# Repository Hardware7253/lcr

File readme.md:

# LCR Meter

## Description
This LCR meter is capable of measuring complex impedance of various passive components and features auto-ranging.
Figure 1 shows the basic test circuit and provides an equation that can be used to calculate the impedance of the DUT.
This circuit + additional filtering and biasing is used within the LCR design.
The MCU software uses the pk-pk values of the sampled waveforms for magnitudes, and calculates the phase difference using in-phase and quadrature components of the multiplied current and test voltage waveforms (v3 & v2). The IQ components are low-pass-filtered, then their arctan is taken to find the phase difference.

Figure 1: Basic LCR testing circuit.

## Demos

## Additional photos

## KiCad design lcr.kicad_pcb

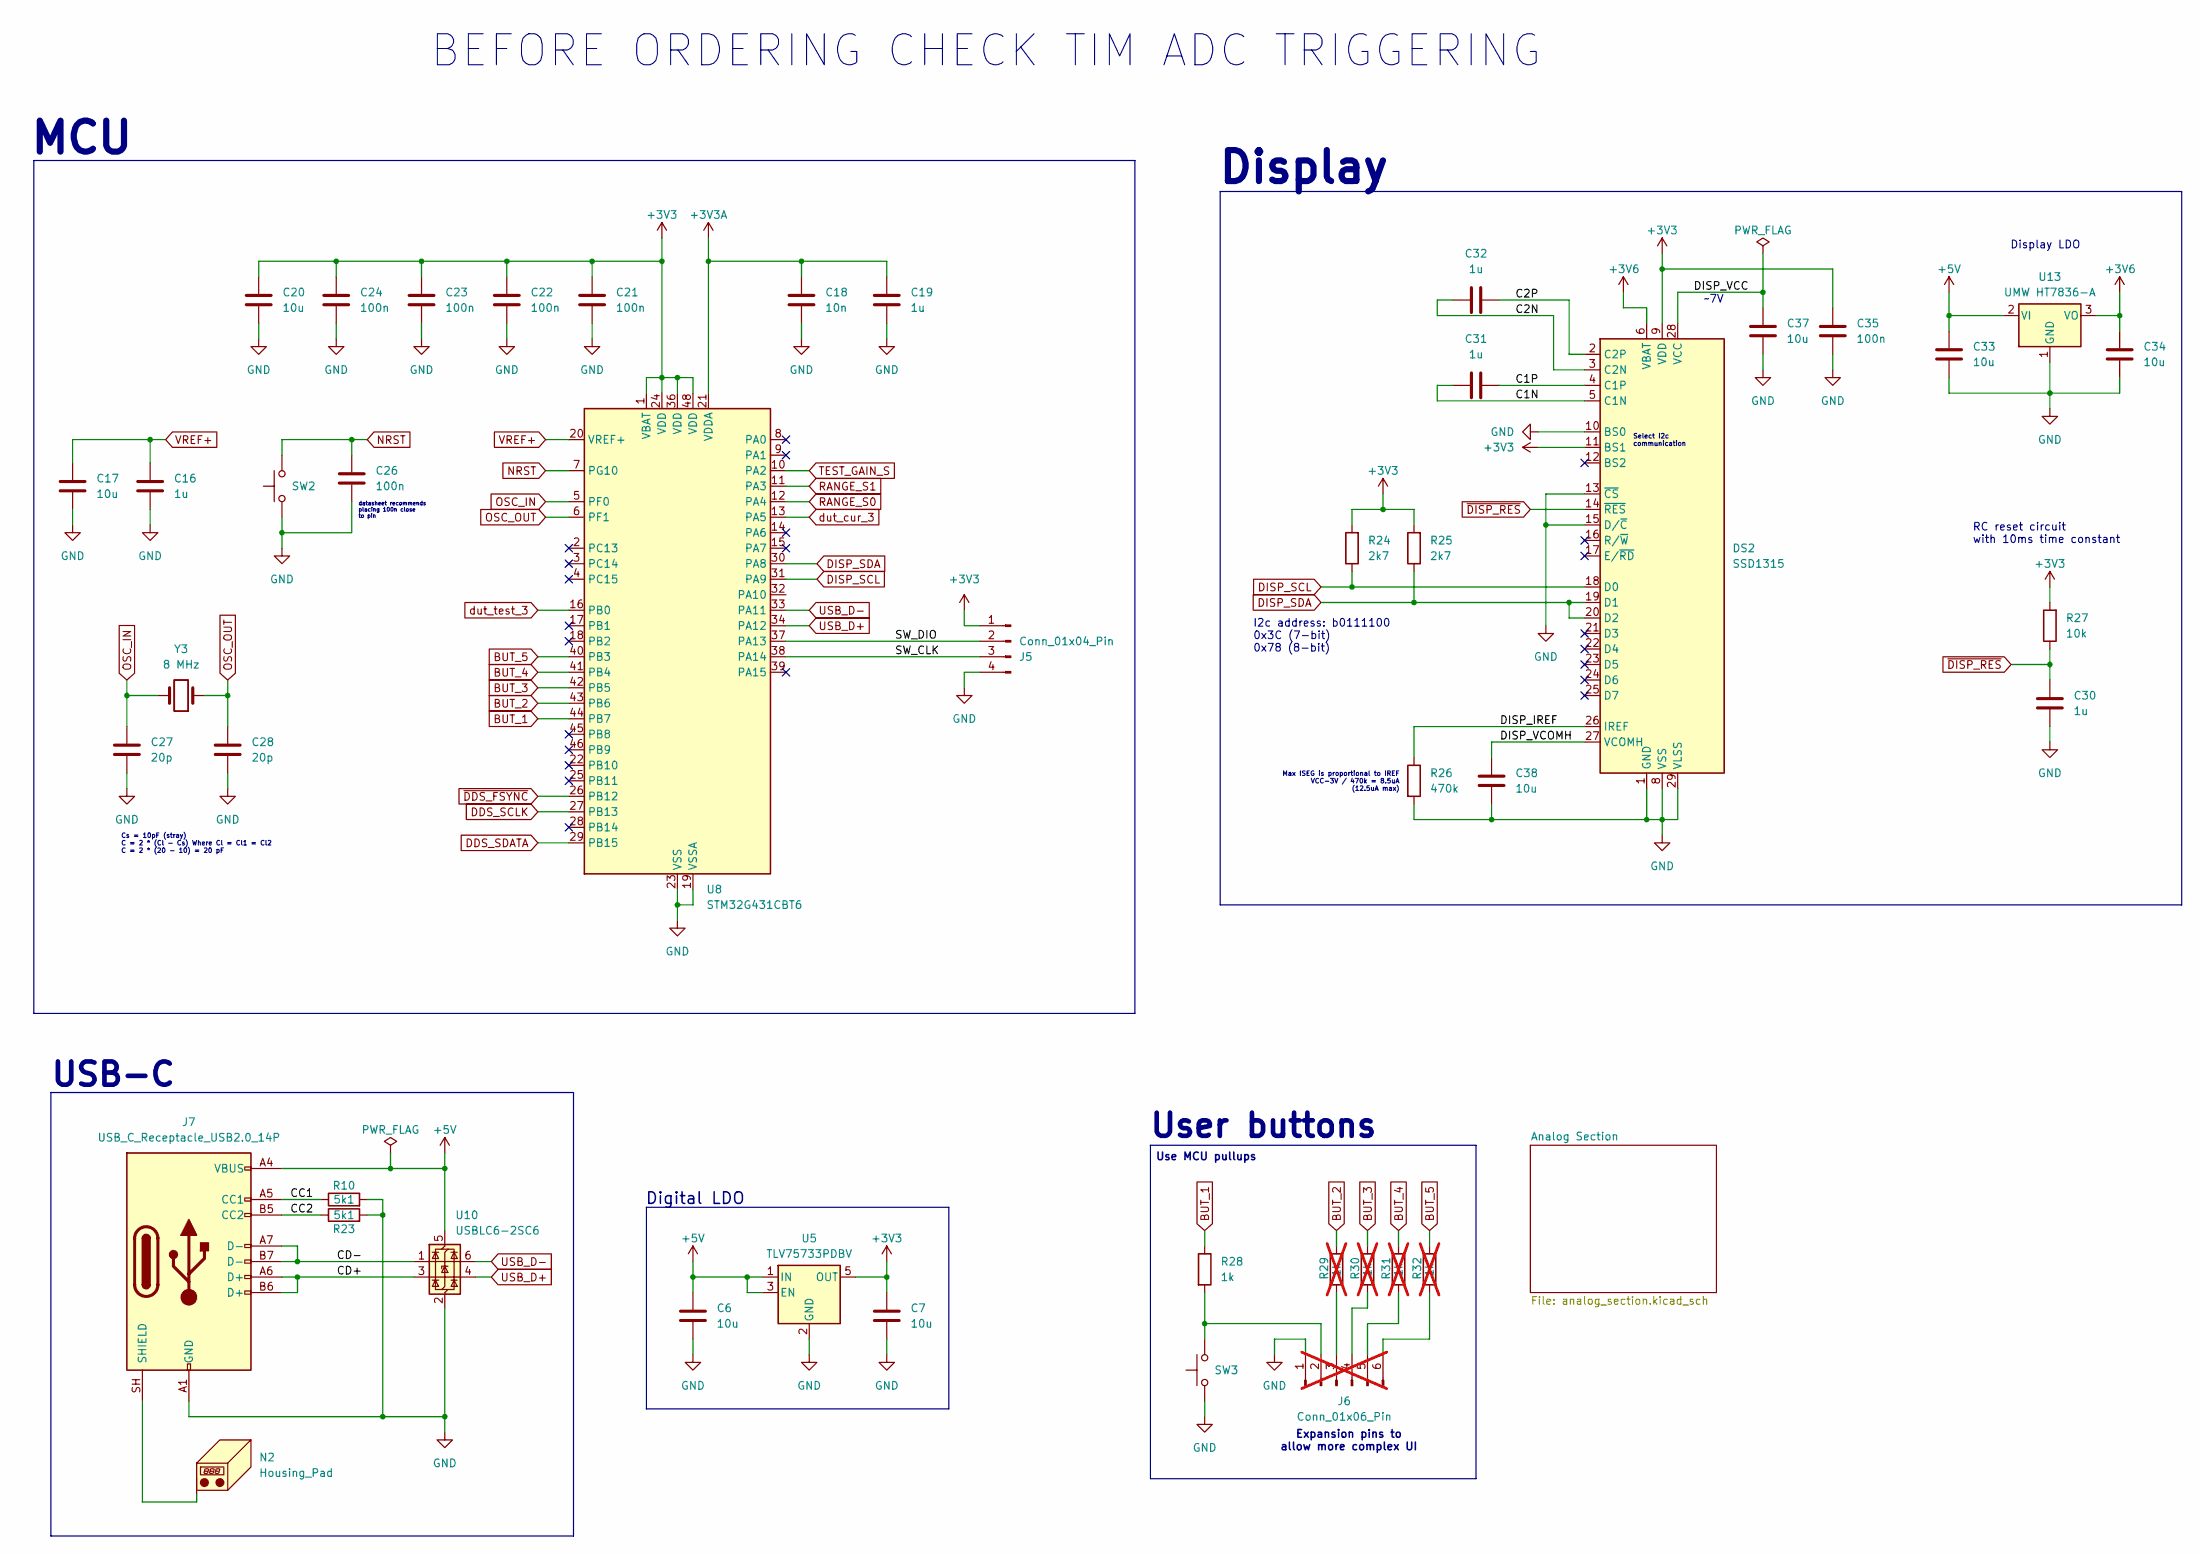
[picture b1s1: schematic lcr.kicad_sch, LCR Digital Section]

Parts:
C6, C7, C17, C20, C33, C34, C37, C38: 10u; C_0603_1608Metric; LCSC PART # C96446
C16, C19, C30, C31, C32: 1u; C_0603_1608Metric; LCSC PART # C15849
C18: 10n; C_0603_1608Metric; LCSC PART # C57112
C21, C22, C23, C24, C26, C35: 100n; C_0603_1608Metric; LCSC PART # C14663
C27, C28: 20p; C_0603_1608Metric; LCSC PART # C326779
DS2: SSD1315; 0.96 Inch OLED Display; LCSC PART # C18723027/C262645
J5: Conn_01x04_Pin; PinHeader_1x04_P2.54mm_Vertical
J6: Conn_01x06_Pin; PinHeader_1x06_P2.54mm_Vertical; not fitted
J7: USB_C_Receptacle_USB2.0_14P; USB_TYPE-C-31-M-12; LCSC PART # C165948
N2: Housing_Pad; TestPoint_Pad_2.0x2.0mm
R10, R23: 5k1; R_0603_1608Metric; LCSC PART # C23186
R24, R25: 2k7; R_0603_1608Metric; LCSC PART # C114612
R26: 470k; R_0603_1608Metric; LCSC PART # C114622
R27: 10k; R_0603_1608Metric; LCSC PART # C25804
R28: 1k; R_0603_1608Metric; LCSC PART # C22548
R29, R30, R31, R32: 1k; R_0603_1608Metric; LCSC PART # C22548; not fitted
SW2, SW3: SW_Push; Korean Hroparts Elec K2-1107ST-A4DW-06; LCSC PART # C118141
U5: TLV75733PDBV; SOT-23-5; LCSC PART # C485517
U8: STM32G431CBT6; LQFP-48_7x7mm_P0.5mm; LCSC PART # C529355
U10: USBLC6-2SC6; SOT-23-6; LCSC PART # C7519
U13: UMW HT7836-A; SOT-89-3
Y3: 8 MHz; Crystal_SMD_5032-2Pin_5.0x3.2mm; LCSC PART # C46613796

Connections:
+3V3: C7.2, C20.2, C21.1, C22.1, C23.1, C24.1, C35.1, DS2.9 (VDD), DS2.11 (BS1), J5.1, R24.2, R25.2, R27.2, U5.5 (OUT), U8.1 (VBAT), U8.24 (VDD), U8.36 (VDD), U8.48 (VDD); also elsewhere on the board
+3V3A: C18.1, C19.1, U8.21 (VDDA); also elsewhere on the board
+3V6: C34.2, DS2.6 (VBAT), U13.3 (VO)
+5V: C6.2, C33.2, J7.A4 (VBUS), J7.A9 (VBUS), J7.B4 (VBUS), J7.B9 (VBUS), U5.1 (IN), U5.3 (EN), U10.5 (VBUS), U13.2 (VI); also elsewhere on the board
/C1N: C31.1, DS2.5 (C1N)
/C1P: C31.2, DS2.4 (C1P)
/C2N: C32.1, DS2.3 (C2N)
/C2P: C32.2, DS2.2 (C2P)
/CC1: J7.A5 (CC1), R10.1
/CC2: J7.B5 (CC2), R23.1
/CD+: J7.A6 (D+), J7.B6 (D+), U10.3 (I/O2)
/CD-: J7.A7 (D-), J7.B7 (D-), U10.1 (I/O1)
/DISP_IREF: DS2.26 (IREF), R26.1
/DISP_VCC: C37.2, DS2.28 (VCC)
/DISP_VCOMH: C38.2, DS2.27 (VCOMH)
/SW_CLK: J5.3, U8.38 (PA14)
/SW_DIO: J5.2, U8.37 (PA13)
BUT_1: R28.1, U8.44 (PB7)
BUT_2: R29.1, U8.43 (PB6)
BUT_3: R30.1, U8.42 (PB5)
BUT_4: R31.1, U8.41 (PB4)
BUT_5: R32.1, U8.40 (PB3)
DDS_SCLK: U8.27 (PB13); also elsewhere on the board
DDS_SDATA: U8.29 (PB15); also elsewhere on the board
DISP_SCL: DS2.18 (D0), R24.1, U8.31 (PA9)
DISP_SDA: DS2.19 (D1), DS2.20 (D2), R25.1, U8.30 (PA8)
GND: C6.1, C7.1, C16.2, C17.2, C18.2, C19.2, C20.1, C21.2, C22.2, C23.2, C24.2, C26.2, C27.2, C28.2, C30.2, C33.1, C34.1, C35.2, C37.1, C38.1, DS2.1 (GND), DS2.8 (VSS), DS2.10 (BS0), DS2.13 (~CS), DS2.15 (D/~C), DS2.29 (VLSS), DS2.30 (GND), J5.4, J6.1, J7.A1 (GND), J7.A12 (GND), J7.B1 (GND), J7.B12 (GND), R10.2, R23.2, R26.2, SW2.1, SW3.1, U5.2 (GND), U8.19 (VSSA), U8.23 (VSS), U8.35 (VSS), U8.47 (VSS), U10.2 (GND), U13.1 (GND); also elsewhere on the board
NRST: C26.1, SW2.2, U8.7 (PG10)
unnamed: J6.2, R28.2, SW3.2
unnamed: J6.3, R29.2
unnamed: J6.4, R30.2
unnamed: J6.5, R31.2
unnamed: J6.6, R32.2
unnamed: J7.SH (SHIELD), N2.1 (PAD_1)
OSC_IN: C27.1, U8.5 (PF0), Y3.2
OSC_OUT: C28.1, U8.6 (PF1), Y3.1
RANGE_S0: U8.12 (PA4); also elsewhere on the board
RANGE_S1: U8.11 (PA3); also elsewhere on the board
TEST_GAIN_S: U8.10 (PA2); also elsewhere on the board
USB_D+: U8.34 (PA12), U10.4 (I/O2)
USB_D-: U8.33 (PA11), U10.6 (I/O1)
VREF+: C16.1, C17.1, U8.20 (VREF+)
dut_cur_3: U8.13 (PA5); also elsewhere on the board
dut_test_3: U8.16 (PB0); also elsewhere on the board
~DDS_FSYNC: U8.26 (PB12); also elsewhere on the board
~DISP_RES: C30.1, DS2.14 (~RES), R27.1

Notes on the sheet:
Max ISEG is proportional to IREF VCC-3V / 470k = 8.5uA (12.5uA max)
Display LDO
Cs = 10pF (stray) C = 2 * (Cl - Cs) Where Cl = Cl1 = Cl2 C = 2 * (20 - 10) = 20 pF
User buttons
Digital LDO
I2c address: b0111100 0x3C (7-bit) 0x78 (8-bit)
USB-C
RC reset circuit with 10ms time constant
~7V
Use MCU pullups
Select i2c communication
MCU
datasheet recommends placing 100n close to pin
Expansion pins to allow more complex UI
Display
BEFORE ORDERING CHECK TIM ADC TRIGGERING

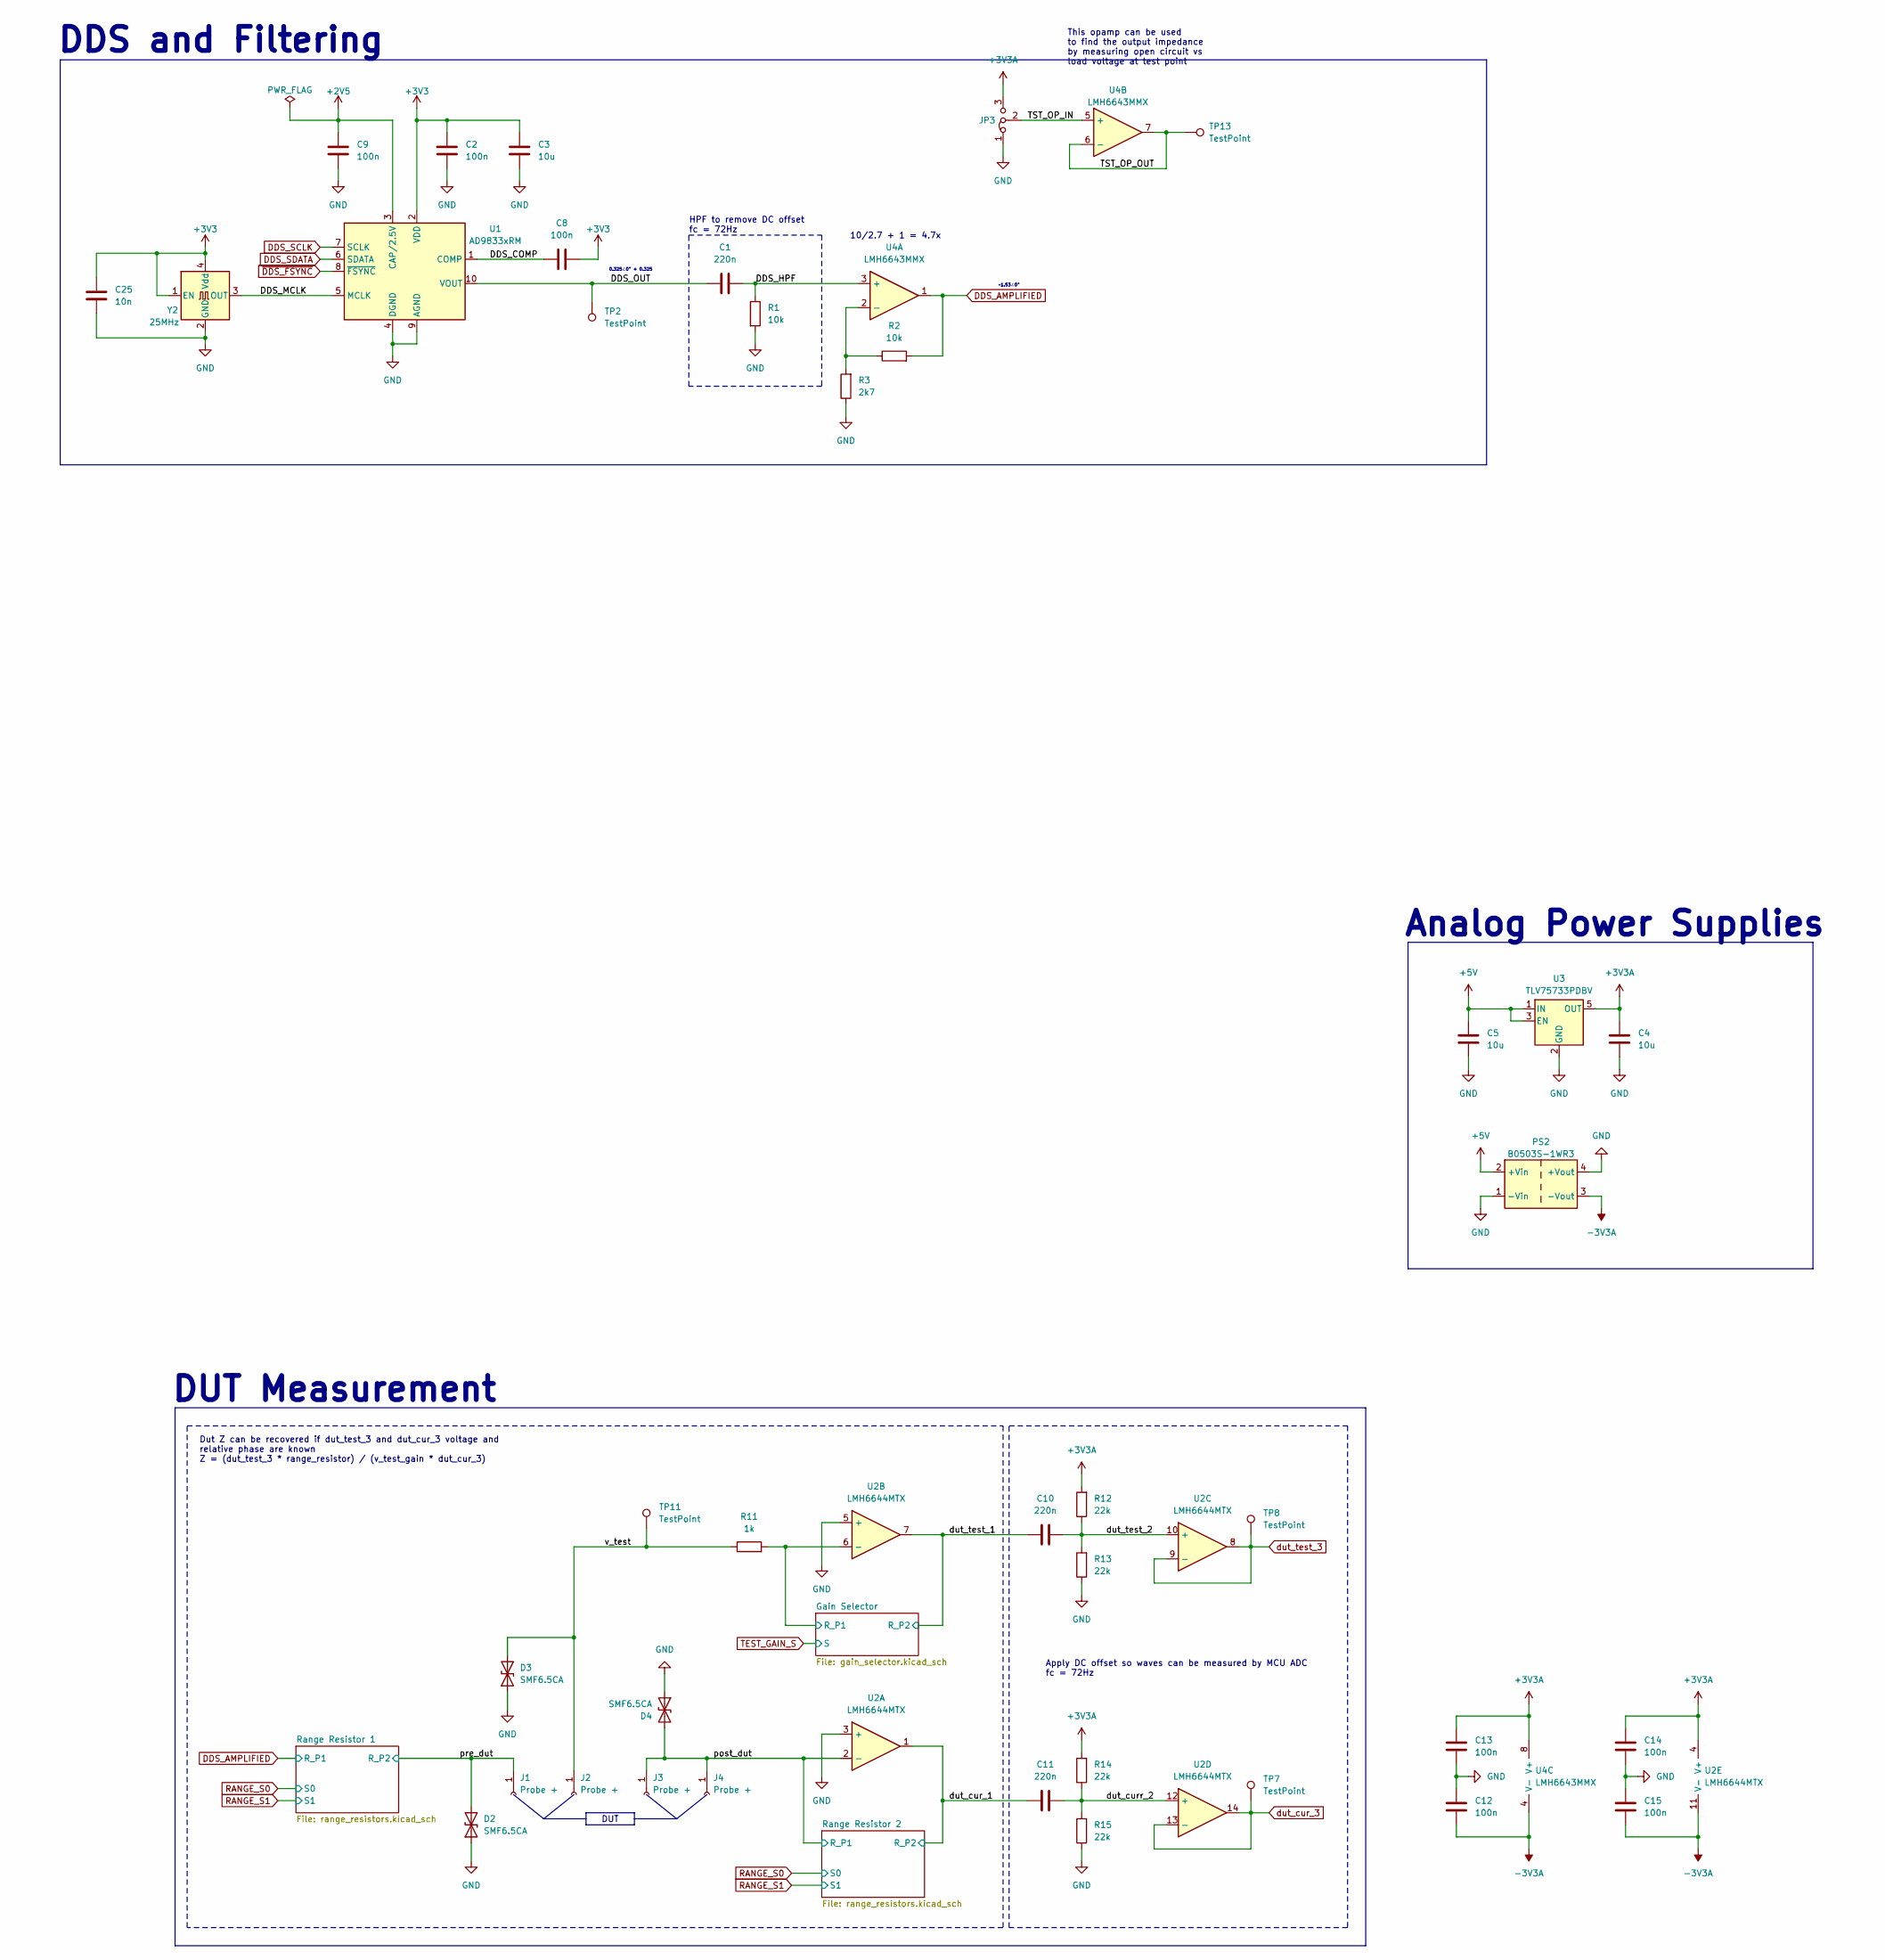
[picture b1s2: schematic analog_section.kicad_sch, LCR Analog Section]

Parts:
C1, C10, C11: 220n; C_0603_1608Metric; LCSC PART # C14663
C2, C8, C9, C12, C13, C14, C15: 100n; C_0603_1608Metric; LCSC PART # C14663
C3, C4, C5: 10u; C_0603_1608Metric; LCSC PART # C96446
C25: 10n; C_0603_1608Metric; LCSC PART # C57112
D2, D3, D4: SMF6.5CA; Nexperia_CFP3_SOD-123W; LCSC PART # C7466385
J1, J2: Probe +; Banana_Cliff_FCR7350R_S16N-PC_Horizontal; LCSC PART # C7437326
J3, J4: Probe +; Banana_Cliff_FCR7350B_S16N-PC_Horizontal; LCSC PART # C7437327
JP3: Jumper_3_Bridged12; PinHeader_1x03_P2.54mm_Vertical
PS2: B0503S-1WR3; Converter_DCDC_Murata_MEE1SxxxxSC_THT; LCSC PART # C7465187
R1, R2: 10k; R_0603_1608Metric; LCSC PART # C25804
R3: 2k7; R_0603_1608Metric; LCSC PART # C114612
R11: 1k; R_0603_1608Metric; LCSC PART # C22548
R12, R13, R14, R15: 22k; R_0603_1608Metric; LCSC PART # C114065
TP2, TP7, TP8, TP11, TP13: TestPoint; TestPoint_Keystone_5000-5004_Miniature; LCSC PART # C5199801
U1: AD9833xRM; MSOP-10_3x3mm_P0.5mm; LCSC PART # C9652
U2: LMH6644MTX; TSSOP-14_4.4x5mm_P0.65mm; LCSC PART # C962081
U3: TLV75733PDBV; SOT-23-5; LCSC PART # C485517
U4: LMH6643MMX; VSSOP-8_3x3mm_P0.65mm; LCSC PART # C478382
Y2: 25MHz; Oscillator_SMD_Abracon_ASE-4Pin_3.2x2.5mm; LCSC PART # C49207939

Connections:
+2V5: C9.2, U1.3 (CAP/2.5V)
+3V3: C2.2, C3.2, C8.1, C25.1, U1.2 (VDD), Y2.1 (EN), Y2.4 (Vdd); also elsewhere on the board
+3V3A: C4.2, C13.2, C14.2, JP3.3 (B), R12.2, R14.2, U2.4 (V+), U3.5 (OUT), U4.8 (V+); also elsewhere on the board
+5V: C5.2, PS2.2 (+Vin), U3.1 (IN), U3.3 (EN); also elsewhere on the board
-3V3A: C12.1, C15.1, PS2.3 (-Vout), U2.11 (V-), U4.4 (V-); also elsewhere on the board
/Analog Section/DDS_COMP: C8.2, U1.1 (COMP)
/Analog Section/DDS_HPF: C1.2, R1.1, U4.3 (+)
/Analog Section/DDS_MCLK: U1.5 (MCLK), Y2.3 (OUT)
/Analog Section/DDS_OUT: C1.1, TP2.1 (1_1), U1.10 (VOUT)
/Analog Section/Gain Selector/R_P1: R11.2, U2.6 (-); also elsewhere on the board
/Analog Section/TST_OP_IN: JP3.2 (C), U4.5 (+)
/Analog Section/TST_OP_OUT: TP13.1 (1_1), U4.6 (-), U4.7
/Analog Section/dut_cur_1: C11.1, U2.1; also elsewhere on the board
/Analog Section/dut_curr_2: C11.2, R14.1, R15.2, U2.12 (+)
/Analog Section/dut_test_1: C10.1, U2.7; also elsewhere on the board
/Analog Section/dut_test_2: C10.2, R12.1, R13.2, U2.10 (+)
/Analog Section/post_dut: D4.2 (A2), J3.1 (Pin_1_1), J4.1 (Pin_1_1), U2.2 (-); also elsewhere on the board
/Analog Section/pre_dut: D2.2 (A2), J1.1 (Pin_1_1); also elsewhere on the board
/Analog Section/v_test: D3.2 (A2), J2.1 (Pin_1_1), R11.1, TP11.1 (1_1)
DDS_AMPLIFIED: R2.2, U4.1; also elsewhere on the board
DDS_SCLK: U1.7 (SCLK); also elsewhere on the board
DDS_SDATA: U1.6 (SDATA); also elsewhere on the board
GND: C2.1, C3.1, C4.1, C5.1, C9.1, C12.2, C13.1, C14.1, C15.2, C25.2, D2.1 (A1), D3.1 (A1), D4.1 (A1), JP3.1 (A), PS2.1 (-Vin), PS2.4 (+Vout), R1.2, R3.1, R13.1, R15.1, U1.4 (DGND), U1.9 (AGND), U2.3 (+), U2.5 (+), U3.2 (GND), Y2.2 (GND); also elsewhere on the board
unnamed: R2.1, R3.2, U4.2 (-)
dut_cur_3: TP7.1 (1_1), U2.13 (-), U2.14; also elsewhere on the board
dut_test_3: TP8.1 (1_1), U2.8, U2.9 (-); also elsewhere on the board
~DDS_FSYNC: U1.8 (~FSYNC); also elsewhere on the board

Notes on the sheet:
DUT
HPF to remove DC offset fc = 72Hz
DUT Measurement
This opamp can be used to find the output impedance by measuring open circuit vs load voltage at test point
Analog Power Supplies
Dut Z can be recovered if dut_test_3 and dut_cur_3 voltage and relative phase are known Z = (dut_test_3 * range_resistor) / (v_test_gain * dut_cur_3)
DDS and Filtering
~1.53∠0°
Apply DC offset so waves can be measured by MCU ADC fc = 72Hz
10/2.7 + 1 = 4.7x
0.325∠0° + 0.325

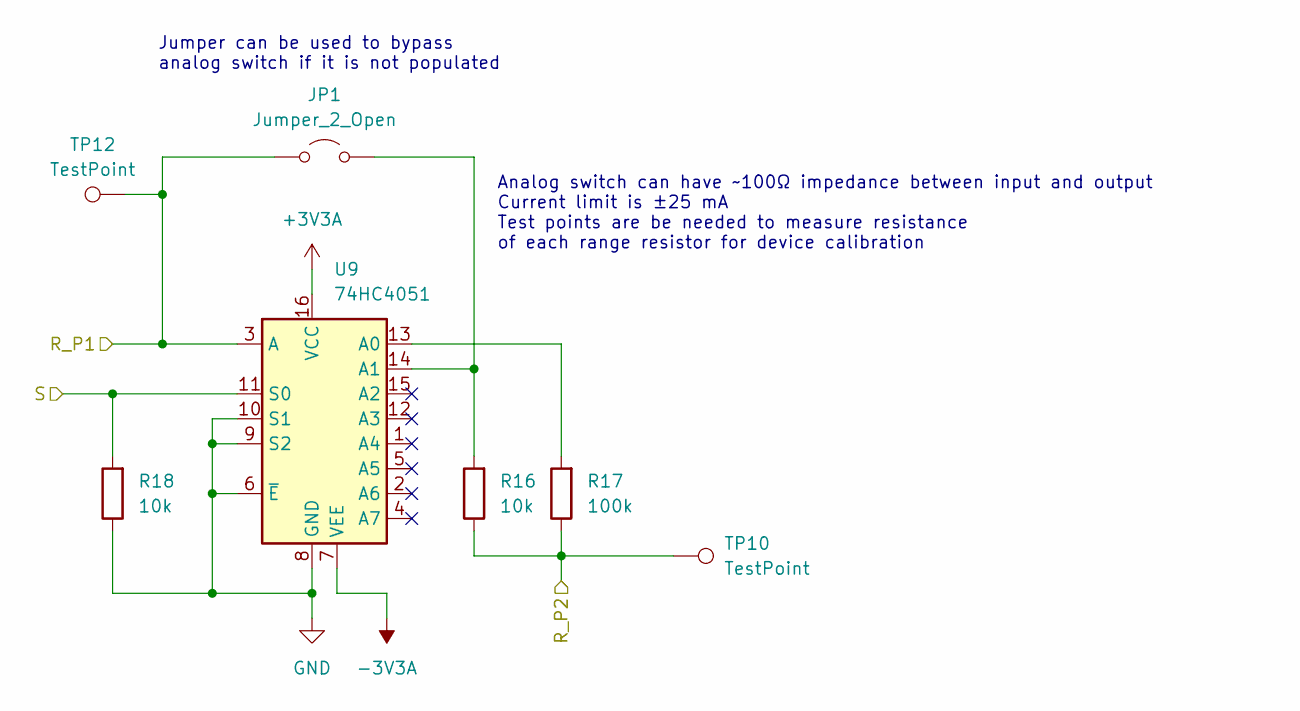
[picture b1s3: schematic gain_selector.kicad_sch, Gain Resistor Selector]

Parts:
JP1: Jumper_2_Open; SolderJumper-2_P1.3mm_Open_TrianglePad1.0x1.5mm
R16, R18: 10k; R_0603_1608Metric; LCSC PART # C25804
R17: 100k; R_0603_1608Metric; LCSC PART # C25803
TP10, TP12: TestPoint; TestPoint_Keystone_5000-5004_Miniature; LCSC PART # C5199801
U9: 74HC4051; SOIC-16_3.9x9.9mm_P1.27mm; LCSC PART # C9386

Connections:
+3V3A: U9.16 (VCC); also elsewhere on the board
-3V3A: U9.7 (VEE); also elsewhere on the board
/Analog Section/Gain Selector/R_P1: JP1.1 (A), TP12.1 (1_1), U9.3 (A); also elsewhere on the board
/Analog Section/dut_test_1: R16.1, R17.1, TP10.1 (1_1); also elsewhere on the board
GND: R18.1, U9.6 (~E), U9.8 (GND), U9.9 (S2), U9.10 (S1); also elsewhere on the board
unnamed: JP1.2 (B), R16.2, U9.14 (A1)
unnamed: R17.2, U9.13 (A0)
TEST_GAIN_S: R18.2, U9.11 (S0); also elsewhere on the board

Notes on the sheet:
Jumper can be used to bypass analog switch if it is not populated
Analog switch can have ~100Ω impedance between input and output Current limit is ±25 mA Test points are be needed to measure resistance of each range resistor for device calibration

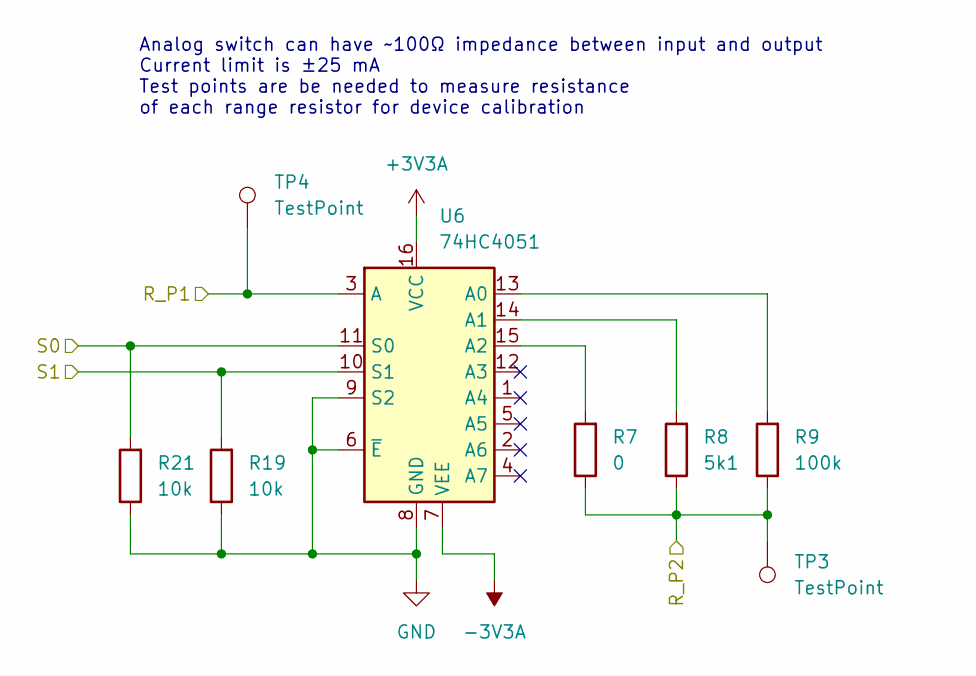
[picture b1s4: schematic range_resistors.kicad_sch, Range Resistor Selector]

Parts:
R7: 0; R_0603_1608Metric
R8: 5k1; R_0603_1608Metric; LCSC PART # C23186
R9: 100k; R_0603_1608Metric; LCSC PART # C25803
R19, R21: 10k; R_0603_1608Metric; LCSC PART # C25804
TP3, TP4: TestPoint; TestPoint_Keystone_5000-5004_Miniature; LCSC PART # C5199801
U6: 74HC4051; SOIC-16_3.9x9.9mm_P1.27mm; LCSC PART # C9386

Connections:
+3V3A: U6.16 (VCC); also elsewhere on the board
-3V3A: U6.7 (VEE); also elsewhere on the board
/Analog Section/pre_dut: R7.1, R8.1, R9.1, TP3.1 (1_1); also elsewhere on the board
DDS_AMPLIFIED: TP4.1 (1_1), U6.3 (A); also elsewhere on the board
GND: R19.1, R21.1, U6.6 (~E), U6.8 (GND), U6.9 (S2); also elsewhere on the board
unnamed: R9.2, U6.13 (A0)
unnamed: R8.2, U6.14 (A1)
unnamed: R7.2, U6.15 (A2)
RANGE_S0: R21.2, U6.11 (S0); also elsewhere on the board
RANGE_S1: R19.2, U6.10 (S1); also elsewhere on the board

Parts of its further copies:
R4: 0; R_0603_1608Metric
R5: 5k1; R_0603_1608Metric; LCSC PART # C23186
R6: 100k; R_0603_1608Metric; LCSC PART # C25803
R20, R22: 10k; R_0603_1608Metric; LCSC PART # C25804
TP5, TP6: TestPoint; TestPoint_Keystone_5000-5004_Miniature; LCSC PART # C5199801
U7: 74HC4051; SOIC-16_3.9x9.9mm_P1.27mm; LCSC PART # C9386

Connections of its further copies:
+3V3A: U7.16 (VCC); also elsewhere on the board
-3V3A: U7.7 (VEE); also elsewhere on the board
/Analog Section/dut_cur_1: R4.1, R5.1, R6.1, TP6.1 (1_1); also elsewhere on the board
/Analog Section/post_dut: TP5.1 (1_1), U7.3 (A); also elsewhere on the board
GND: R20.1, R22.1, U7.6 (~E), U7.8 (GND), U7.9 (S2); also elsewhere on the board
unnamed: R6.2, U7.13 (A0)
unnamed: R5.2, U7.14 (A1)
unnamed: R4.2, U7.15 (A2)
RANGE_S0: R22.2, U7.11 (S0); also elsewhere on the board
RANGE_S1: R20.2, U7.10 (S1); also elsewhere on the board

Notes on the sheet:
Analog switch can have ~100Ω impedance between input and output Current limit is ±25 mA Test points are be needed to measure resistance of each range resistor for device calibration

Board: 2 copper layers, 109 parts (1 on the bottom side), 71 nets, no tracks yet.

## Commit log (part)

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2026-04-11 First commit
    Commiting before adding LPF
2026-04-12 Did some routing
    Commiting before changing display from i2c to spi
2026-04-12 Done
    Schematics and PCB are "done".
    Meaning I've just finished but need to review
    the design before it's ready to order.
2026-04-13 Added polish
2026-04-25 Changed range resistor selector design
    Changed range resistor selector from an analog mux
    to a MOSFET BPS design. This should improve on resistance, linearity,
    and temperature stability for the range resistors.
2026-04-27 Started new layout
    Range resistors now use MOSFET BPS.
    Currently there's no protection for over voltage on the opamp or mcu
    inputs, so that needs to be done.
2026-05-06 Added protection to MCU analog inputs
    DUT and test voltages now use clamping diodes to protect the MCU from
    voltages less than 0V and greater than 3.3V.
    Started laying out again, but thinking of trying something different
    with the layou of the range resistors around the 1st opamp.
2026-05-06 Done new layout
    Now need to polish again. Also should test BPS
    in the flesh and innevetably scrap half the current schematic
    and layout when it doesn't work as expected.
2026-05-07 Polished PCB
2026-05-15 Added gate drive current limiting resistors
2026-05-16 Add prototype code
    Code was for a breadboard prototype with a development board, but should
    be useful for the final design.
2026-05-20 Added case design for 3d printing
2026-05-23 Changed code to work on final hardware
    The code now uses the stm32g4xx C HAL, as opposed to the old stm32f4xx
    HAL used for the breadboard prototype. I don't have hardware at this
    point so I can't test, the sampling code at this point is placeholder
    that likely needs fixing. Anyway it compiles.
2026-06-03 Fixed some PCB bugs
    The OLED display ribbon cable folded the wrong way so the screen faced
    down, so I fixed that. Also made vias untented, made diodes
    easier to hand solder, and added ground test hook.
    The case CAD still needs to be updated.
2026-06-09 Fixed gate drive comp ref
    Resistors in the voltage divider were the wrong way around, now it's
    correct. Also fixed the linker script, so the compiled code now uploads
    to the board. Verified DDS works, and LMH6643 has 21.56 ohm output
    impedance at DC. CAD still need updating.
2026-06-16 Added extra configuration for TIM, ADCs and DMAs
    I think the ADC clock speed needs adjusting
2026-06-20 Sampling now works correctly
    Enabling the dma mux clock and enabling internal voltage reference where
    previously missing. Now these are implemented and things are working
    enough that a device can be measured.
2026-06-24 Added display hello world
2026-06-26 Fixed OLED display hardware and code
    On the schematic, the OLED pin D2 was left NC, but needed to be tied to
    D1. Also the u8g2 SPI code from the last commit was incorrect, as it
    didn't use 9-bit SPI mode which is necessary for 3-wire SPI communcation
    with the display. I fixed this, and also modified the hardware to allow
    4-wire and 3-wire SPI. I'll change the code over to 4-wire when I order
    new PCBs.
2026-06-30 Range resistors now use signal relays
    Most of the analog section layout was completely overhauled to fit this
    change.
2026-06-30 Removed old schematic sheets
